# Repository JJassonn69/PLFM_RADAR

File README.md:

# AERIS-10: Open Source Pulse Linear Frequency Modulated Phased Array Radar

AERIS-10 is an open-source, low-cost 10.5 GHz phased array radar system featuring Pulse Linear Frequency Modulated (LFM) modulation. Available in two versions (3km and 20km range), it's designed for researchers, drone developers, and serious SDR enthusiasts who want to explore and experiment with phased array radar technology.

## 📡 Overview

The AERIS-10 project aims to democratize radar technology by providing a fully open-source, modular, and hackable radar system. Whether you're a university researcher, a drone startup, or an advanced maker, AERIS-10 offers a platform for experimenting with beamforming, pulse compression, Doppler processing, and target tracking.

## 🔬 Key Features

- **Open Source Hardware & Software** - Complete schematics, PCB layouts, firmware, and software available
- **Dual Version Availability**:
  - **AERIS-10N (Nexus)**: 3km range with 8x16 patch antenna array
  - **AERIS-10E (Extended)**: 20km range with 32x16 dielectric-filled slotted waveguide array
- **Full Electronic Beam Steering** - ±45° electronic steering in elevation and azimuth
- **Advanced Signal Processing** - On-board FPGA handles pulse compression, Doppler FFT, MTI, and CFAR
- **Python GUI** - User-friendly interface with map integration
- **GPS/IMU Integration** - Real-time position and attitude correction
- **Modular Design** - Separate power management, frequency synthesis, and RF boards

## 🏗️ System Architecture

### Hardware Components

The AERIS-10 main sub-systems are:

- **Power Management Board** - Supplies all necessary voltage levels to the electronics components with proper filtering and sequencing (sequencing ensured by the microcontroller)

- **Frequency Synthesizer Board** - Uses a high-performance Low Jitter Clock Generator (AD9523-1) that supplies phase-aligned clock references for:
  - RX and TX Frequency Synthesizers (ADF4382)
  - DAC
  - ADC
  - FPGA

- **Main Board** containing:
  - **DAC** - Generates the RADAR Chirps
  - **2x Microwave Mixers (LTC5552)** - For up-conversion and IF-down-conversion
  - **4x 4-Channel Phase Shifters (ADAR1000)** - For RX and TX chain beamforming
  - **16x Front End Chips (ADTR1107)** - Used for both Low Noise Amplifying (RX) and Power Amplifying (TX) stages
  - **XC7A50T FPGA** - Handles RADAR Signal Processing on the upstream FTG256 board:
    - PLFM Chirps generation via the DAC
    - Raw ADC data read
    - Hybrid Automatic Gain Control (AGC) — cross-layer FPGA/STM32/GUI loop
    - I/Q Baseband Down-Conversion
    - Decimation
    - Filtering
    - Forward FFT
    - Pulse Compression
    - Doppler, MTI and CFAR processing
    - USB Interface
  - **STM32F746xx Microcontroller** - Used for:
    - Power-up and power-down sequencing (see Power Management Excel File)
    - FPGA communication
    - Setup and Interface with:
      - Clock Generator (AD9523-1)
      - 2x Frequency Synthesizers (ADF4382)
      - 4x 4-Channel Phase Shifters (ADAR1000) for RADAR pulse sequencing
      - 2x ADS7830 8-channel I²C ADCs (Main Board, U88 @ 0x48 / U89 @ 0x4A) for 16x Idq measurement, one per PA channel, each sensed through a 5 mΩ shunt on the PA board and an INA241A3 current-sense amplifier (x50) on the Main Board
      - 2x DAC5578 8-channel I²C DACs (Main Board, U7 @ 0x48 / U69 @ 0x49) for 16x Vg control, one per PA channel; closed-loop calibrated at boot to the target Idq
      - GPS module (UM982) for GUI map centering and per-detection position tagging
      - GY-85 IMU for pitch/roll correction of target coordinates
      - BMP180 Barometer
      - Stepper Motor
      - 1x ADS7830 8-channel I²C ADC (Main Board, U10) reading 8 thermistors for thermal monitoring; a single GPIO (EN_DIS_COOLING) switches the cooling fans on when any channel exceeds the threshold
      - RF switches

- **16x Power Amplifier Boards** - Used only for AERIS-10E version, featuring 10Watt QPA2962 GaN amplifier for extended range

- **Antenna Arrays**:
  - **AERIS-10N (Nexus)** - 8x16 patch antenna array
  - **AERIS-10X (Extended)** - 32x16 dielectric-filled slotted waveguide antenna array

- **Miscellaneous Components**:
  - Slip-Ring
  - Stepper Motor and drivers
  - Cooling Fans
  - Enclosure

### Processing Pipeline

1. **Waveform Generation** - DAC creates LFM chirps
2. **Up/Down Conversion** - LTC5552 mixers handle frequency translation
3. **Beam Steering** - ADAR1000 phase shifters control 16 elements
4. **Signal Processing (FPGA)**:
   - Raw ADC data capture
   - I/Q baseband down-conversion
   - Decimation & filtering (CIC/FIR)
   - Pulse compression
   - Doppler FFT processing
   - MTI & CFAR detection
5. **System Management (STM32)**:
   - Power sequencing
   - Peripheral configuration
   - GPS/IMU integration
   - Stepper motor control
6. **Visualization (Python GUI)**:
   - Real-time target plotting
   - Map integration
   - Radar control interface

<!-- V6 GIF removed — V6 is deprecated. V65 Tk and V7 PyQt6 are the active GUIs. -->

## 📊 Technical Specifications

| Parameter | AERIS-10N (Nexus) | AERIS-10X (Extended) |
|-----------|-------------------|----------------------|
| **Frequency** | 10.5 GHz | 10.5 GHz |
| **Max Range** | 3 km | 20 km |
| **Antenna** | 8x16 Patch Array | 32x16 Slotted Waveguide |
| **Beam Steering** | Electronic (±45°) | Electronic (±45°) |
| **Mechanical Scan** | 360° (stepper motor) | 360° (stepper motor) |
| **Output Power** | ~1W×16 | 10W×16 (GaN amplifier) |
| **Processing** | FPGA + STM32 | FPGA + STM32 |

## 🚀 Getting Started

### 🧹 Repository File Placement Policy

To keep the repository root clean and make artifacts easy to find, place generated files in the following locations:

- **Published reports (tracked, GitHub Pages):** `docs/`
  - Example: `docs/AERIS_Simulation_Report_v2.pdf`
- **Simulation-generated outputs (local, gitignored):** `5_Simulations/generated/`
  - Plots, scenario outputs, temporary analysis directories
- **FPGA/Vivado generated artifacts (local, gitignored):** `9_Firmware/9_2_FPGA/reports/`
  - VCD/VVP dumps, temporary CSVs, local report snapshots
- **Reusable FPGA automation scripts (tracked):** `9_Firmware/9_2_FPGA/scripts/`
  - TCL flows, helper scripts used by build/bring-up

**Do not leave generated artifacts in the repository root.**

### Prerequisites

- Basic understanding of radar principles
- Experience with PCB assembly (for hardware build)
- Python 3.8+ for the GUI software
- FPGA development tools (Vivado) for signal processing modifications

### Hardware Assembly

1. **Order PCBs**: Production outputs are under `/4_Schematics and Boards Layout/4_7_Production Files`
2. **Source Components**: BOM/CPL files are co-located under `/4_Schematics and Boards Layout/4_7_Production Files`
3. **Assembly**: Use the schematics in `/4_Schematics and Boards Layout/4_6_Schematics` together with the production outputs above; a standalone assembly guide is not currently tracked
4. **Antenna**: Choose appropriate array files for your target variant
5. **Enclosure**: Mechanical drawings currently live in `/8_Utils/Mechanical_Drawings`

## 📜 License

This project is open-source but uses **different licenses for hardware and software** to ensure proper legal coverage.

### Hardware Documentation
The hardware design files—including:
- Schematics and PCB layouts (in `/4_Schematics and Boards Layout`)
- Bill of Materials (BOM) files
- Gerber files and manufacturing outputs
- Mechanical drawings and enclosure designs

are licensed under the **CERN Open Hardware Licence Version 2 – Permissive (CERN-OHL-P)** .

This is a hardware-specific license that:
- ✅ Clearly defines "Hardware," "Documentation," and "Products"
- ✅ Includes explicit patent protection for contributors and users
- ✅ Provides stronger liability limitations (important for high-power RF)
- ✅ Aligns with professional open-hardware standards (CERN, OSHWA)

You may use, modify, and sell products based on these designs, provided you:
- Maintain the original copyright notices
- Distribute any modified designs under the same license
- Make your modifications available in Source format

### Software and Firmware
The software components—including:
- FPGA code (VHDL/Verilog in `/9_Firmware`)
- Microcontroller firmware (STM32)
- Python GUI and utilities

remain under the **MIT License** for maximum flexibility.

### Full License Texts
- The complete CERN-OHL-P license text is in the `LICENSE` file
- MIT license terms apply to software where not otherwise specified

### Why This Change?
Originally, the entire project used the MIT license. The community (special thanks to gmaynez!) pointed out that MIT lacks legal protections needed for physical hardware. The switch to CERN-OHL-P ensures the project is properly protected while maintaining the same permissive spirit.

## 📚 Documentation

Comprehensive documentation is available in the `/docs` folder and served via GitHub Pages at [https://NawfalMotii79.github.io/PLFM_RADAR/docs/](https://NawfalMotii79.github.io/PLFM_RADAR/docs/):

- [System Architecture](/docs/architecture.html)
- [Implementation Log](/docs/implementation-log.html)
- [Hardware Bring-Up Guide](/docs/bring-up.html)
- [Test Reports](/docs/reports.html)
- [Release Notes](/docs/release-notes.html)

## 🤝 Contributing

We welcome contributions! Please see our [Contributing Guidelines](/CONTRIBUTING.md) for details on repo layout, branch workflow, and basic PR checks.

Areas where help is especially appreciated:
- **RF Engineers**: Review designs, optimize antenna performance
- **FPGA Developers**: Optimize signal processing pipeline
- **Software Developers**: Enhance Python GUI and SDK
- **Beta Testers**: University researchers, drone startups, advanced makers

## 📞 Contact & Collaboration

I welcome serious inquiries from researchers, engineers, and potential collaborators. However, due to the high volume of interest in this project, please understand that I cannot guarantee a response to every message.

- **Technical questions or bug reports**: Please [open a GitHub issue](https://github.com/NawfalMotii79/PLFM_RADAR/issues) so the whole community can benefit from the discussion.
- **Collaboration, licensing, or business inquiries**: 📧 nawfal.motii.33 [at] gmail [dot] com

## 💰 Sponsors

---

**Star ⭐ this repository if you're interested in open-source radar technology!**

*Note: This is an active development project. Some features are still in progress. Check the issues page for known limitations and upcoming features.*

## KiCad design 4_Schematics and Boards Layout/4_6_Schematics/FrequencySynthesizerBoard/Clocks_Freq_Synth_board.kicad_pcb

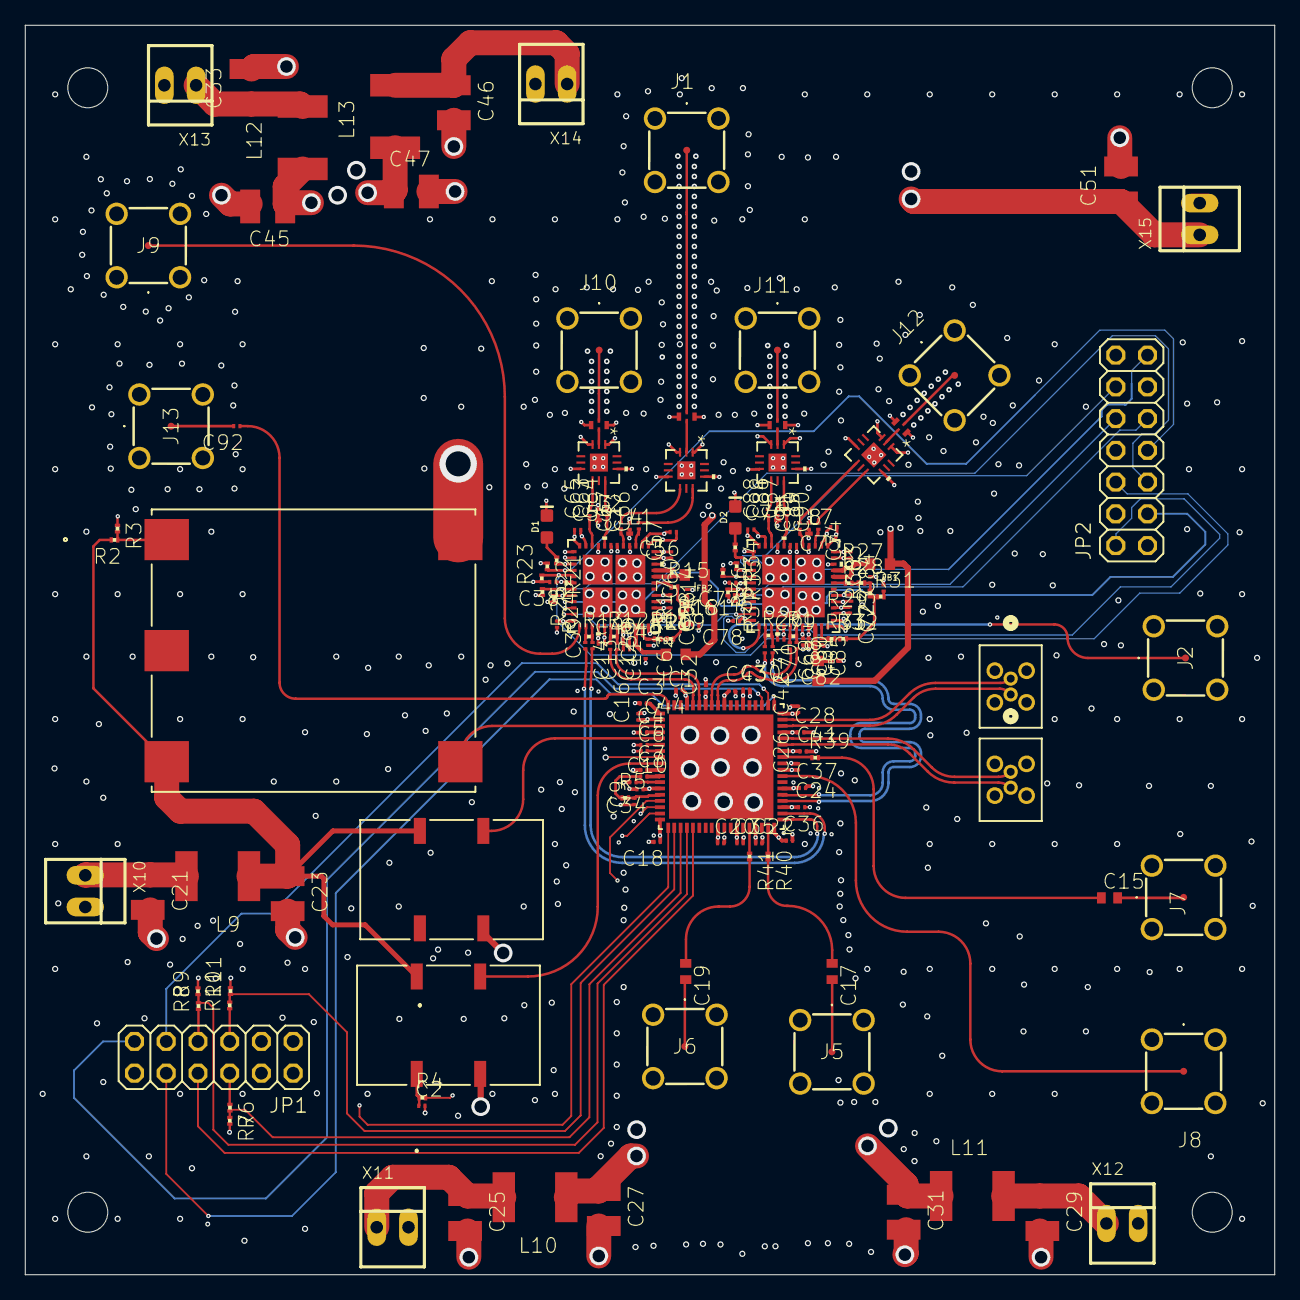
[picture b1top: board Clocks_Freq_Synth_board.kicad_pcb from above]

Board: 6 copper layers, 100.0 x 100.0 mm, 188 parts (0 on the bottom side), 134 nets.

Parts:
C1, C62, C63, C85, C86, C89: 10pF; C0201_334
C2, C6: 0.33µF; C0201_334
C3: 0.47µf; C0201_334
C4, C5, C7: C0201_334
C8: 1000pF; C0201_334
C9, C10: 0.47µF; C0201_334
C11, C12, C13, C14, C59, C68, C69, C70, C71, C82: 1µF; C0201_334
C15, C17, C19: 10nF; C0402_334
C16, C18, C20, C22, C24, C26, C28, C30, C32, C34, C35, C36, C37, C41, C42, C43, C44, C64, C65, C66, C67, C87, C88, C90, C91: 0.1µF; C0201_334
C21, C25, C29, C33, C46, C51: 22µF; C1210_334
C23, C27, C31, C45, C47: 10µF; C1210_334
C38, C39, C40, C48, C49, C50, C55, C56, C57, C58, C72, C73, C74, C75, C76, C77, C78, C79, C80, C81: 4.7µF; C0201_334
C60, C83: 31pF; C0201_334
C61, C84: 10nF; C0201_334
C92: 0.1µf; C0201_334
D1, D2: Green; LED-0603
FB1, FB2, FB3, FB4: FBMH1608HL601-T; BEADC1608X90N
IC1: AD9523BCPZ; QFN50P1000X1000X100-73N
J1, J2, J5, J6, J7, J8, J9, J10, J11, J12, J13: 142-0731-211; 1420731211
J3, J4: CJT-T-P-HH-ST-TH1; CONN_CJT-T-P-XX-ST-TH1_SAI
JP1: 2X06_325
JP2: 2X07_325
L1, L2, L3, L4, L5, L6, L7, L8: 1.3nH; L0201_334
L9, L10, L11, L12, L13: L5650M_334
R1, R12, R13, R26: 100R; R0201_334
R2, R3, R4, R7, R9, R11: 1k; R0201_334
R5, R14, R15, R19, R20, R27, R28, R32, R33: 0R; R0201_334
R6, R8, R10: 0.65k; R0201_334
R16, R29: 931R; R0201_334
R17, R30: 30R; R0201_334
R18, R31: 330R; R0201_334
R21, R34: 500R; R0201_334
R22, R23, R24, R25, R35, R36, R37, R38: 200k; R0201_334
R39, R40, R41: 22R; R0201_334
U1, U6: ADF4382ABCCZ; CC-48-10_ADI
U2, U3, U7, U9: MTX2-143+; DQ1225_MNC
U4, U5, U8, U10: ATS1005-3DB-FD-T05; SMT_DB-FD-T05_SUS
UNK_HOLE_0: dummyfp0
UNK_HOLE_1: dummyfp1
UNK_HOLE_2: dummyfp2
UNK_HOLE_3: dummyfp3
X4: ECOC-2522-100.000-3HC; SMD5_ECOC-2522_25P4X22_ECS
X5, X6: CVHD-950-50.000; SMD4_CVHD-950_CRX
X10, X11, X12, X13, X14, X15: 22-23-2021; 22-23-2021_165

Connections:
10MHZ_OUT: IC1.3, X4.4
100MHZ_OUT: IC1.5, X5.3
+1V8_CLOCK: C31.1, C35.1, C36.1, C37.1, C41.1, C42.1, C43.1, C44.1, IC1.30, IC1.36, IC1.42, IC1.48, IC1.54, IC1.63, IC1.69, L11.1
+3V3_CLOCK: C16.1, C18.1, C20.1, C22.1, C24.1, C26.1, C27.1, C28.1, C30.1, C32.1, C34.1, IC1.2, IC1.13, IC1.18, IC1.27, IC1.33, IC1.39, IC1.45, IC1.51, IC1.60, IC1.66, L10.1
+3V3_LO_1: C38.1, C39.1, C40.1, C45.1, C48.1, C49.1, C50.1, C72.1, C77.1, C78.1, C79.1, C80.1, C81.1, L12.1, R24.2, R25.2, R37.2, R38.2, U1.3, U1.30, U1.36, U1.40, U1.44, U1.45, U6.3, U6.30, U6.36, U6.40, U6.44, U6.45
+3V3_LO_2: C1.1, C47.1, C55.1, C56.1, C57.1, C58.1, C63.1, C73.1, C74.1, C75.1, C76.1, C86.1, C89.1, L1.1, L2.1, L3.2, L4.2, L5.1, L6.2, L7.1, L8.2, L13.1, U1.5, U1.11, U1.13, U1.24, U6.5, U6.11, U6.13, U6.24
+3V3_XO: C23.1, L9.1, R2.2, X4.3, X5.4, X6.4
+5V0_LO: C51.1, FB1.1, FB2.1, FB3.2, FB4.2, X15.1
AD9523_CS: JP1.5, R10.1
AD9523_EEPROM_SEL: IC1.57, JP1.11
AD9523_OUT0_N: C11.2, IC1.67
AD9523_OUT0_P: C12.2, IC1.68
AD9523_OUT1_N: C68.2, IC1.64
AD9523_OUT1_P: C69.2, IC1.65
AD9523_OUT4_N: IC1.52, J3.2
AD9523_OUT4_P: IC1.53, J3.1
AD9523_OUT5_N: IC1.49, J4.2
AD9523_OUT5_P: IC1.50, J4.1
AD9523_OUT6+: C15.2, J7.1
AD9523_OUT7+: IC1.44, J8.1
AD9523_OUT8_N: C70.2, IC1.40
AD9523_OUT8_P: C71.2, IC1.41
AD9523_OUT9_N: C13.2, IC1.37
AD9523_OUT9_P: C14.2, IC1.38
AD9523_OUT10+: IC1.35, R40.1
AD9523_OUT11+: IC1.32, R41.1
AD9523_PD: IC1.15, JP1.1
AD9523_REF_SEL: IC1.16, JP1.2
AD9523_RESET: IC1.19, JP1.4
AD9523_SCLK: JP1.6, R6.1
AD9523_SDIO: JP1.7, R8.1
AD9523_SDO: IC1.23, JP1.8
AD9523_STATUS0: IC1.56, JP1.9
AD9523_STATUS1: IC1.55, JP1.10
AD9523_SYNC: IC1.17, JP1.3
ADF4382_RX_CE: JP2.10, R38.1, U6.31
ADF4382_RX_CS: JP2.9, R37.1, U6.32
ADF4382_RX_DELADJ: JP2.12, R35.2, U6.28
ADF4382_RX_DELSTR: JP2.11, R36.2, U6.29
ADF4382_RX_LKDET: JP2.13, R34.2, U6.27
ADF4382_RX_SYNC_N: C70.1, R26.2, U6.39
ADF4382_RX_SYNC_P: C71.1, R26.1, U6.38
ADF4382_SCLK: JP2.2, U1.34, U6.34
ADF4382_SDIO: JP2.3, U1.33, U6.33
ADF4382_SDO: JP2.1, U1.35, U6.35
ADF4382_TX_CE: JP2.5, R25.1, U1.31
ADF4382_TX_CS: JP2.4, R24.1, U1.32
ADF4382_TX_DELADJ: JP2.7, R22.2, U1.28
ADF4382_TX_DELSTR: JP2.6, R23.2, U1.29
ADF4382_TX_LKDET: JP2.8, R21.2, U1.27
ADF4382_TX_SYNC_N: C13.1, R13.2, U1.39
ADF4382_TX_SYNC_P: C14.1, R13.1, U1.38
GND: C1.2, C2.2, C3.1, C4.1, C5.1, C6.1, C7.1, C9.1, C10.1, C16.2, C18.2, C20.2, C21.2, C22.2, C23.2, C24.2, C25.2, C26.2, C27.2, C28.2, C29.2, C30.2, C31.2, C32.2, C33.2, C34.2, C35.2, C36.2, C37.2, C38.2, C39.2, C40.2, C41.2, C42.2, C43.2, C44.2, C45.2, C46.2, C47.2, C48.2, C49.2, C50.2, C51.2, C55.2, C56.2, C57.2, C58.2, C59.1, C60.2, C61.2, C62.2, C63.2, C72.2, C73.2, C74.2, C75.2, C76.2, C77.2, C78.2, C79.2, C80.2, C81.2, C82.1, C83.2, C84.2, C85.2, C86.2, C89.2, D1.C, D2.C, IC1.73, J1.2, J1.3, J1.4, J1.5, J2.2, J2.3, J2.4, J2.5, J5.2, J5.3, J5.4, J5.5, J6.2, J6.3, J6.4, J6.5, J7.2, J7.3, J7.4, J7.5, J8.2, J8.3, J8.4, J8.5, J9.2, J9.3, J9.4, J9.5, J10.2, J10.3, J10.4, J10.5, J11.2, J11.3, J11.4, J11.5, J12.2, J12.3, J12.4, J12.5, J13.2, J13.3, J13.4, J13.5, JP1.12, JP2.14, R3.1, R7.2, R9.2, R11.2, R22.1, R23.1, R35.1, R36.1, U1.1, U1.2, U1.4, U1.10, U1.12, U1.14, U1.16, U1.18, U1.19, U1.21, U1.23, U1.25, U1.26, U1.41, U1.48, U1.49, U1.50, U1.51, U1.52, U2.1, U2.3, U2.6, U2.10, U2.13, U3.1, U3.3, U3.6, U3.10, U3.13, U4.3, U4.4, U5.3, U5.4, U6.1, U6.2, U6.4, U6.10, U6.12, U6.14, U6.16, U6.18, U6.19, U6.21, U6.23, U6.25, U6.26, U6.41, U6.48, U6.49, U6.50, U6.51, U6.52, U7.1, U7.3, U7.6, U7.10, U7.13, U8.3, U8.4, U9.1, U9.3, U9.6, U9.10, U9.13, U10.3, U10.4, X4.5, X5.2, X6.2, X10.2, X11.2, X12.2, X13.2, X14.2, X15.2
unnamed: R2.1, R3.2, X4.1
unnamed: C2.1, R4.1, X6.1
unnamed: C3.2, IC1.1
unnamed: C6.2, IC1.7
unnamed: C4.2, IC1.4
unnamed: C5.2, IC1.6
unnamed: C7.2, IC1.10
unnamed: C8.2, IC1.11
unnamed: C8.1, R5.1
unnamed: C9.2, IC1.14, R5.2
unnamed: C10.2, IC1.12
unnamed: IC1.21, R6.2, R7.1
unnamed: IC1.22, R8.2, R9.1
unnamed: IC1.20, R10.2, R11.1
unnamed: C11.1, R12.2, U1.43
unnamed: C12.1, R12.1, U1.42
unnamed: C61.1, R18.2
unnamed: R14.1, U1.9
unnamed: FB2.2, R14.2, U1.8
unnamed: C59.2, FB3.1, U1.46
unnamed: R19.1, R20.2
unnamed: R15.1, U1.7
unnamed: R15.2, R16.2
unnamed: C60.1, R16.1, R17.2
unnamed: R17.1, R18.1, R19.2
unnamed: C62.1, R20.1, U1.47
unnamed: U2.2, U4.1
unnamed: C65.2, U2.7
unnamed: J10.1, U4.2
unnamed: C64.2, U2.9
unnamed: C67.2, U3.7
unnamed: C66.2, U3.9
unnamed: U3.2, U5.1
unnamed: J1.1, U5.2
unnamed: D1.A, R21.1
unnamed: J9.1, U1.37
unnamed: C68.1, R1.2, U6.43
unnamed: C69.1, R1.1, U6.42
unnamed: R27.1, U6.9
unnamed: FB1.2, R27.2, U6.8
unnamed: C82.2, FB4.1, U6.46
unnamed: C84.1, R31.2
unnamed: R32.1, R33.2
unnamed: R28.1, U6.7
unnamed: R28.2, R29.2
unnamed: C83.1, R29.1, R30.2
unnamed: R30.1, R31.1, R32.2
unnamed: C85.1, R33.1, U6.47
unnamed: D2.A, R34.1
unnamed: J2.1, U6.37
unnamed: C88.2, U7.7
unnamed: C87.2, U7.9
unnamed: U7.2, U8.1
unnamed: J11.1, U8.2
unnamed: C91.2, U9.7
unnamed: C90.2, U9.9
unnamed: U9.2, U10.1
unnamed: J12.1, U10.2
unnamed: C92.1, IC1.72
unnamed: C92.2, J13.1
unnamed: IC1.47, R39.1
unnamed: C15.1, R39.2
unnamed: C17.2, J5.1
unnamed: C17.1, R40.2
unnamed: C19.2, J6.1
unnamed: C19.1, R41.2
unnamed: C21.1, L9.2, X10.1
unnamed: C25.1, L10.2, X11.1
unnamed: C29.1, L11.2, X12.1
unnamed: C33.1, L12.2, X13.1
unnamed: C46.1, L13.2, X14.1
OSC_CTRL: IC1.8, R4.2
RX_RFOUT_1_N: C87.1, L5.2, U6.20
RX_RFOUT_1_P: C88.1, L6.1, U6.22
RX_RFOUT_2_N: C90.1, L7.2, U6.15
RX_RFOUT_2_P: C91.1, L8.1, U6.17
TX_RFOUT_1_N: C64.1, L2.2, U1.20
TX_RFOUT_1_P: C65.1, L3.1, U1.22
TX_RFOUT_2_N: C66.1, L1.2, U1.15
TX_RFOUT_2_P: C67.1, L4.1, U1.17
VCXO_OUT: IC1.9, X6.3

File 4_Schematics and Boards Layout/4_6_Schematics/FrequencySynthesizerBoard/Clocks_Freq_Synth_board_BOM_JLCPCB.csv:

Comment,Designator,Footprint,LCSC Part #
10pF,"C1,C62,C63,C85,C86,C89",C0201_334,C106245
0.33µF,"C2,C6",C0201_334,C331029
0.47µf,C3,C0201_334,C331025
DNP,"C4,C5,C7",C0201_334,
1000pF,C8,C0201_334,C106246
0.47µF,"C9,C10",C0201_334,C331025
1µF,"C11,C12,C13,C14,C59,C68,C69,C70,C71,C82",C0201_334,C106253
10nF,"C15,C17,C19",C0402_334,C15195
0.1µF,"C16,C18,C20,C22,C24,C26,C28,C30,C32,C34,C35,C36,C37,C41,C42,C43,C44,C64,C65,C66,C67,C87,C88,C90,C91",C0201_334,C106250
22µF,"C21,C25,C29,C33,C46,C51",C1210_334,C108816
10µF,"C23,C27,C31,C45,C47",C1210_334,C108812
4.7µF,"C38,C39,C40,C48,C49,C50,C55,C56,C57,C58,C72,C73,C74,C75,C76,C77,C78,C79,C80,C81",C0201_334,C106258
31pF,"C60,C83",C0201_334,
10nF,"C61,C84",C0201_334,C106247
0.1µf,C92,C0201_334,C106250
Green,"D1,D2",LED-0603,C72043
FBMH1608HL601-T,"FB1,FB2,FB3,FB4",BEADC1608X90N,C96445
AD9523BCPZ,IC1,QFN50P1000X1000X100-73N,
142-0731-211,"J1,J2,J5,J6,J7,J8,J9,J10,J11,J12,J13",1420731211,
CJT-T-P-HH-ST-TH1,"J3,J4",CONN_CJT-T-P-XX-ST-TH1_SAI,
DNP,JP1,2X06_325,
DNP,JP2,2X07_325,
1.3nH,"L1,L2,L3,L4,L5,L6,L7,L8",L0201_334,
DNP,"L9,L10,L11,L12,L13",L5650M_334,
100R,"R1,R12,R13,R26",R0201_334,C106230
1k,"R2,R3,R4,R7,R9,R11",R0201_334,C106232
0R,"R5,R14,R15,R19,R20,R27,R28,R32,R33",R0201_334,C106222
0.65k,"R6,R8,R10",R0201_334,
931R,"R16,R29",R0201_334,
30R,"R17,R30",R0201_334,C106228
330R,"R18,R31",R0201_334,C106231
500R,"R21,R34",R0201_334,
200k,"R22,R23,R24,R25,R35,R36,R37,R38",R0201_334,C106240
22R,"R39,R40,R41",R0201_334,C106227
ADF4382ABCCZ,"U1,U6",CC-48-10_ADI,
MTX2-143+,"U2,U3,U7,U9",DQ1225_MNC,
ATS1005-3DB-FD-T05,"U4,U5,U8,U10",SMT_DB-FD-T05_SUS,
ECOC-2522-100.000-3HC,X4,SMD5_ECOC-2522_25P4X22_ECS,
CVHD-950-50.000,"X5,X6",SMD4_CVHD-950_CRX,
22-23-2021,"X10,X11,X12,X13,X14,X15",22-23-2021_165,

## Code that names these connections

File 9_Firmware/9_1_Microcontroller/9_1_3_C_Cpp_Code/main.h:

/* USER CODE BEGIN Header */
/**
  ******************************************************************************
  * @file           : main.h
  * @brief          : Header for main.c file.
  *                   This file contains the common defines of the application.
  ******************************************************************************
  * @attention
  *
  * Copyright (c) 2025 STMicroelectronics.
  * All rights reserved.
  *
  * This software is licensed under terms that can be found in the LICENSE file
  * in the root directory of this software component.
  * If no LICENSE file comes with this software, it is provided AS-IS.
  *
  ******************************************************************************
  */
/* USER CODE END Header */

/* Define to prevent recursive inclusion -------------------------------------*/
#ifndef __MAIN_H
#define __MAIN_H

#ifdef __cplusplus
extern "C" {
#endif

/* Includes ------------------------------------------------------------------*/
#include "stm32f7xx_hal.h"

/* Private includes ----------------------------------------------------------*/
/* USER CODE BEGIN Includes */

/* USER CODE END Includes */

/* Exported types ------------------------------------------------------------*/
/* USER CODE BEGIN ET */
extern uint8_t GUI_start_flag_received;
extern uint8_t USB_Buffer[64];

/* USER CODE END ET */

/* Exported constants --------------------------------------------------------*/
/* USER CODE BEGIN EC */

/* USER CODE END EC */

/* Exported macro ------------------------------------------------------------*/
/* USER CODE BEGIN EM */

/* USER CODE END EM */

/* Exported functions prototypes ---------------------------------------------*/
void Error_Handler(void);

/* USER CODE BEGIN EFP */

/* USER CODE END EFP */

/* Private defines -----------------------------------------------------------*/
#define AD9523_PD_Pin GPIO_PIN_3
#define AD9523_PD_GPIO_Port GPIOF
#define AD9523_REF_SEL_Pin GPIO_PIN_4
#define AD9523_REF_SEL_GPIO_Port GPIOF
#define AD9523_SYNC_Pin GPIO_PIN_5
#define AD9523_SYNC_GPIO_Port GPIOF
#define AD9523_RESET_Pin GPIO_PIN_6
#define AD9523_RESET_GPIO_Port GPIOF
#define AD9523_CS_Pin GPIO_PIN_7
#define AD9523_CS_GPIO_Port GPIOF
#define AD9523_STATUS0_Pin GPIO_PIN_8
#define AD9523_STATUS0_GPIO_Port GPIOF
#define AD9523_STATUS1_Pin GPIO_PIN_9
#define AD9523_STATUS1_GPIO_Port GPIOF
#define AD9523_EEPROM_SEL_Pin GPIO_PIN_10
#define AD9523_EEPROM_SEL_GPIO_Port GPIOF
#define ADAR_1_CS_3V3_Pin GPIO_PIN_0
#define ADAR_1_CS_3V3_GPIO_Port GPIOA
#define ADAR_2_CS_3V3_Pin GPIO_PIN_1
#define ADAR_2_CS_3V3_GPIO_Port GPIOA
#define ADAR_3_CS_3V3_Pin GPIO_PIN_2
#define ADAR_3_CS_3V3_GPIO_Port GPIOA
#define ADAR_4_CS_3V3_Pin GPIO_PIN_3
#define ADAR_4_CS_3V3_GPIO_Port GPIOA
#define LED_1_Pin GPIO_PIN_12
#define LED_1_GPIO_Port GPIOF
#define LED_2_Pin GPIO_PIN_13
#define LED_2_GPIO_Port GPIOF
#define LED_3_Pin GPIO_PIN_14
#define LED_3_GPIO_Port GPIOF
#define LED_4_Pin GPIO_PIN_15
#define LED_4_GPIO_Port GPIOF
#define EN_P_5V0_PA1_Pin GPIO_PIN_0
#define EN_P_5V0_PA1_GPIO_Port GPIOG
#define EN_P_5V0_PA2_Pin GPIO_PIN_1
#define EN_P_5V0_PA2_GPIO_Port GPIOG
#define EN_P_1V0_FPGA_Pin GPIO_PIN_7
#define EN_P_1V0_FPGA_GPIO_Port GPIOE
#define EN_P_1V8_FPGA_Pin GPIO_PIN_8
#define EN_P_1V8_FPGA_GPIO_Port GPIOE
#define EN_P_3V3_FPGA_Pin GPIO_PIN_9
#define EN_P_3V3_FPGA_GPIO_Port GPIOE
#define EN_P_5V0_ADAR_Pin GPIO_PIN_10
#define EN_P_5V0_ADAR_GPIO_Port GPIOE
#define EN_P_3V3_ADAR12_Pin GPIO_PIN_11
#define EN_P_3V3_ADAR12_GPIO_Port GPIOE
#define EN_P_3V3_ADAR34_Pin GPIO_PIN_12
#define EN_P_3V3_ADAR34_GPIO_Port GPIOE
#define EN_P_3V3_ADTR_Pin GPIO_PIN_13
#define EN_P_3V3_ADTR_GPIO_Port GPIOE
#define EN_P_3V3_SW_Pin GPIO_PIN_14
#define EN_P_3V3_SW_GPIO_Port GPIOE
#define EN_P_3V3_VDD_SW_Pin GPIO_PIN_15
#define EN_P_3V3_VDD_SW_GPIO_Port GPIOE
#define EN_P_5V0_PA3_Pin GPIO_PIN_2
#define EN_P_5V0_PA3_GPIO_Port GPIOG
#define EN_P_5V5_PA_Pin GPIO_PIN_3
#define EN_P_5V5_PA_GPIO_Port GPIOG
#define EN_P_1V8_CLOCK_Pin GPIO_PIN_4
#define EN_P_1V8_CLOCK_GPIO_Port GPIOG
#define EN_P_3V3_CLOCK_Pin GPIO_PIN_5
#define EN_P_3V3_CLOCK_GPIO_Port GPIOG
#define ADF4382_RX_LKDET_Pin GPIO_PIN_6
#define ADF4382_RX_LKDET_GPIO_Port GPIOG
#define ADF4382_RX_DELADJ_Pin GPIO_PIN_7
#define ADF4382_RX_DELADJ_GPIO_Port GPIOG
#define ADF4382_RX_DELSTR_Pin GPIO_PIN_8
#define ADF4382_RX_DELSTR_GPIO_Port GPIOG
#define MAG_DRDY_Pin GPIO_PIN_6
#define MAG_DRDY_GPIO_Port GPIOC
#define ACC_INT_Pin GPIO_PIN_7
#define ACC_INT_GPIO_Port GPIOC
#define GYR_INT_Pin GPIO_PIN_8
#define GYR_INT_GPIO_Port GPIOC
#define STEPPER_CW_P_Pin GPIO_PIN_4
#define STEPPER_CW_P_GPIO_Port GPIOD
#define STEPPER_CLK_P_Pin GPIO_PIN_5
#define STEPPER_CLK_P_GPIO_Port GPIOD
#define EN_DIS_RFPA_VDD_Pin GPIO_PIN_6
#define EN_DIS_RFPA_VDD_GPIO_Port GPIOD
#define EN_DIS_COOLING_Pin GPIO_PIN_7
#define EN_DIS_COOLING_GPIO_Port GPIOD

/* FPGA digital I/O (directly connected GPIOs)
 *   DIG_5 (PD13): signal-saturation flag — input, polled by AGC outer loop
 *                 (gated by !MCU_AGC_FORCE_DISABLED).
 *   DIG_6 (PD14): chirp_scheduler frame_pulse, ~100 ns FPGA-stretched —
 *                 EXTI rising + pulldown; ISR increments g_frame_pulse_count
 *                 (PR-AB.b drift-free dwell sync).
 *   DIG_7 (PD15): control-fault OR (range_decim_watchdog | CIC→FIR overrun) —
 *                 polled by checkSystemHealth stuck-high sampler. */
#define FPGA_DIG5_SAT_Pin       GPIO_PIN_13
#define FPGA_DIG5_SAT_GPIO_Port GPIOD
#define FPGA_DIG6_Pin           GPIO_PIN_14
#define FPGA_DIG6_GPIO_Port     GPIOD
#define FPGA_DIG7_Pin           GPIO_PIN_15
#define FPGA_DIG7_GPIO_Port     GPIOD

/* PR-AB.b: alias names that match the post-Phase-3 role of DIG_6. */
#define FPGA_FRAME_PULSE_Pin       FPGA_DIG6_Pin
#define FPGA_FRAME_PULSE_GPIO_Port FPGA_DIG6_GPIO_Port
#define FPGA_FRAME_PULSE_EXTI_IRQn EXTI15_10_IRQn

/* PR-AB.b expanded commit 5: DIG_0 (PD8) carries the MCU per-beam-pattern
 * ready toggle into the FPGA's chirp_scheduler beam-ready handshake.
 * runRadarPulseSequence toggles this pin once per setCustomBeamPattern16(RX)
 * call after the SPI burst completes, so the FPGA only starts the next 48-
 * chirp frame once the new beam pattern is in place. The FPGA-side stall is
 * gated by opcode 0x1A (host_handshake_enable, cold-reset = 0) so flashing
 * the bitstream before the GUI enables the feature leaves the radar in its
 * legacy open-loop cadence. */
#define FPGA_BEAM_READY_Pin       GPIO_PIN_8
#define FPGA_BEAM_READY_GPIO_Port GPIOD

#define ADF4382_RX_CE_Pin GPIO_PIN_9
#define ADF4382_RX_CE_GPIO_Port GPIOG
#define ADF4382_RX_CS_Pin GPIO_PIN_10
#define ADF4382_RX_CS_GPIO_Port GPIOG
#define ADF4382_TX_LKDET_Pin GPIO_PIN_11
#define ADF4382_TX_LKDET_GPIO_Port GPIOG
#define ADF4382_TX_DELSTR_Pin GPIO_PIN_12
#define ADF4382_TX_DELSTR_GPIO_Port GPIOG
#define ADF4382_TX_DELADJ_Pin GPIO_PIN_13
#define ADF4382_TX_DELADJ_GPIO_Port GPIOG
#define ADF4382_TX_CS_Pin GPIO_PIN_14
#define ADF4382_TX_CS_GPIO_Port GPIOG
#define ADF4382_TX_CE_Pin GPIO_PIN_15
#define ADF4382_TX_CE_GPIO_Port GPIOG
#define DAC_1_VG_CLR_Pin GPIO_PIN_4
#define DAC_1_VG_CLR_GPIO_Port GPIOB
#define DAC_1_VG_LDAC_Pin GPIO_PIN_5
#define DAC_1_VG_LDAC_GPIO_Port GPIOB
#define DAC_2_VG_CLR_Pin GPIO_PIN_8
#define DAC_2_VG_CLR_GPIO_Port GPIOB
#define DAC_2_VG_LDAC_Pin GPIO_PIN_9
#define DAC_2_VG_LDAC_GPIO_Port GPIOB

/* USER CODE BEGIN Private defines */

/* USER CODE END Private defines */

#ifdef __cplusplus
}
#endif

#endif /* __MAIN_H */

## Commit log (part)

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2026-03-20 Complete Diagram
2026-03-22 Add board-day smoke test guide with step-by-step instructions
    Covers:
    - Bitstream inventory (heartbeat v0.1.7, FT601 dev v0.1.8, timing-fix v0.1.9)
    - Hardware setup: TE0713 + TE0701 + UMFT601X-B jumper config
    - 3-stage smoke test: heartbeat → FT601 USB → host commands
    - Host-side smoke_test.py and radar_dashboard.py usage
    - Signal diagnostics table, troubleshooting, known limitations
2026-03-22 Revert "Fix Ctrl+C crash in radar_dashboard.py (GIL + tkinter threading race)"
    This reverts commit 7f0e7b4cac3175e6660dc97f5b219f5a3faf1495.
2026-03-22 Clarify detection scatter coordinate mapping after fftshift
    Add explicit comments explaining how shifted Doppler array indices
    map to velocity coordinates. The coordinate conversion was correct,
    but now it's documented:
    - Shifted index 0 = original bin 16 = -max_vel (most negative)
    - Shifted index 16 = original bin 0 = 0 m/s (DC)
    - Shifted index 31 = original bin 15 = +max_vel (most positive)
2026-03-22 Add --moving-target mode: approaching target with closing range
    Reverted packet alignment fix since diagonal waterfall is correct
    for moving targets (range changes over time = diagonal stripes).
    New --moving-target flag simulates target approaching radar:
    - Target starts at range bin 55 (far, ~280m)
    - Moves toward radar at 0.3 bins/frame (negative velocity)
    - High positive Doppler (Doppler bin 25 = approaching fast)
2026-03-22 Add JLCPCB project rules and refine DRC: 1508 -> 661 violations (9 real errors)
    - Create .kicad_pro with JLCPCB 6-layer design rules (0.1mm clearance,
    0.3mm min via, 0.075mm annular ring, 0.15mm drill/hole)
    - Update .kicad_dru: relax via-to-via clearance from 0.254mm to 0.20mm
    (JLCPCB minimum for 0.15mm drill), eliminating 16 false positives
    - Rewrite DRC fix guide with verified violation counts and streamlined
    path to fab-ready (~30 min manual work remaining)
2026-03-23 Add freq synth board: schematic, gerbers, drills, BOM, DRC-fixed PCB
    Includes:
    - Restored schematic (.kicad_sch) from Eagle import history
    - Sub-schematic sheet (_1.kicad_sch)
    - Eagle import symbol library (.kicad_sym)
    - JLCPCB 6-layer gerber set (F/B/In1-4 Cu, masks, paste, silkscreen)
    - PTH + NPTH drill files with drill map PDF
2026-03-23 Repo cleanup: remove duplicate files, root fix scripts, update README paths
    Deleted (duplicates — identical MD5 copies exist elsewhere):
    - 8_Utils/Antenna_Array.jpg (dup of docs/assets/img/Antenna_Array.jpg)
    - 8_Utils/RADAR_V6.jpg (dup of docs/assets/img/RADAR_V6.jpg)
    - 8_Utils/RADAR_V6_V2.png (dup of 2_Functional Diagram/RADAR_V6_V2.png)
    - 8_Utils/Python/test_radar_data.csv (dup of 9_Firmware/9_3_GUI/test_radar_data.csv)
    - 7_Components Datasheets/AD9484/UG-290.pdf (dup of 6_Application Notes/UG-290.pdf)
2026-03-24 Fix velocity flip: per-dimension clustering + SNR-weighted centroid
    Root cause: euclidean eps=50 merged all detections at same range
    regardless of velocity, causing 48 detections (-24 to +24 m/s) to
    merge into one cluster with meaningless average velocity.
    Fix:
    - Per-dimension box thresholds (range_eps=20m, vel_eps=5m/s)
    - Sort by SNR descending so strongest peaks seed clusters
2026-03-24 Fix UART pin mapping: P16 -> P19 for uart_rxd (MIO14/B14_L24_P)
    Verified via 4x5_series_pinout_tracelength.xlsx that:
    - JB1-91 (MIO14) -> JM1-92 -> FPGA P19 (B14_L24_P), NOT P16
    - JB1-86 (MIO15) -> JM1-85 -> FPGA U18 (B14_L18_N) (was correct)
    Both nets are direct B2B-to-FPGA, NOT routed through TE0713 CPLD U3.
2026-03-24 Fix VIO build: create IP directory before create_ip
2026-03-25 Add GO/SO CFAR mode dropdown, parameter validation, and fix tkinter test deps
    V2 dashboard enhancements:
    - Replace CFAR Mode numeric entry with CA/GO/SO dropdown (ttk.Combobox)
    - Add _send_validated_param() with RTL-accurate range clamping for all params
    - Add CFAR mode indicator in status bar
    Shared constants extracted to radar_protocol.py (tkinter-free):
    - CFAR_MODE_NAMES, CFAR_MODE_VALUES, PARAM_VALIDATION, AERIS10_CONFIG
2026-03-27 Add TCP stream server for remote FPGA visualization over SSH tunnel
    New SocketConnection class in radar_protocol.py provides the same
    interface as FT601Connection but communicates over TCP with a
    length-prefixed protocol. ft601_stream_server.py runs on the remote
    server (with FT601 hardware) and bridges USB reads/writes to TCP.
    Usage: start server on remote, SSH tunnel port 9000, then:
    python3 GUI_radar_dashboard_v2.py --remote localhost:9000
2026-03-28 FPGA v9d: fix Pop FSM pending flag races + USB drain timing
    - Add !usb_X_pending guards to all 3 Pop FSMs (prevents pop-while-pending)
    - Add disabled-stream discard logic in USB FSM IDLE state (prevents deadlock)
    - Add per-type RTL debug counters (consumed/discarded/pending_sets)
    - Fix TB drain timing: wait_ft_clk(20) after FIFO empty before counting
    - Add exact 2048 Doppler count assertion + handshake race checks
    - Clean up verbose debug instrumentation from off-by-one investigation
2026-04-07 docs(readme): add Alpha disclaimer to Key Features
    Core hardware works, but GPS/map integration, attitude correction,
    and beam steering UI are not yet complete — callers deserve to know
    before they build on those features.
    Closes gap 10.5 from reality-check review.
2026-04-20 test(fpga): F-2.2 adversarial mid-frame reset sweep + F-0.1 TB plumbing
    G9B adds a 4-iteration reset sweep on top of the existing e2e harness:
    - Reset is injected at four offsets (3/7/12/18 us) into a steady-state
    auto-scan burst, with mixed short/long hold durations (20-120 clk_100m)
    to exercise asynchronous assert paths through the FSM + CDCs.
    - Each iteration asserts: system_status drops to 0 during reset,
    new_chirp_frame resumes post-release, and obs_range_valid_count
2026-04-20 fix(fpga): F-0.9 option B — FT2232H output_delay 11.667→3.5 ns (TN_167)
    Previous output_delay of 11.667 ns was a synthetic back-calculation
    (period − 5 ns), not a datasheet number. It over-constrained FPGA
    launch by ~8 ns vs the actual FT2232H 245-Sync FIFO setup requirement.
    Per FTDI TN_167:
    - t_su (data to CLKOUT rising): 3.5 ns (was 11.667 — too tight)
    - t_h (data hold after CLKOUT): 1.0 ns (was 0.0 — no hold check)
2026-04-20 merge(wave3/tier2): port testbenches and cosim goldens for fft-2048
    Regression goes from 21/32 -> 27/32 passing.
    TB files updated from feat/fft-2048-upgrade (FFT_SIZE=2048 / 512 range
    bins / Manhattan magnitude / 2-segment matched filter):
    - tb/tb_mf_cosim.v (range_profile_{i,q} port names)
    - tb/tb_matched_filter_processing_chain.v (long_chirp port names)
    - tb/tb_range_bin_decimator.v (new 2048->512 DUT)
2026-04-23 fix: MCU-N4 delay_us bound; GUI-S4 STREAM_CONTROL comment
    MCU-N4: delay_us(us) reset TIM1 then waited for the counter to reach `us`,
    but TIM1 ARR is 0xffff-1 (~65 ms at the 1 MHz tick). Any caller passing
    us > 65534 spun forever after the first wrap — a real hazard with the PA
    energized. Chunk requests larger than ARR into ARR-sized waits, then the
    remainder in the existing single wait. Current callers (T1, PRI1-T1,
    Guard, 500us spots) are all well under the bound; this is defensive.
2026-04-27 fix(gui): GUI-S2 — DataRecorder snapshots arrays before HDF5 write
    The same RadarFrame is enqueued for the display consumer and handed to
    DataRecorder.record_frame on the producer thread. h5py releases the GIL
    during gzip compression, so any in-place mutation by the consumer (or a
    future scaling/normalisation step) would tear the on-disk frame.
    record_frame now copies all five numpy arrays into local snapshots
    before passing them to h5py.create_dataset. Disk integrity no longer
2026-04-29 xdc(200t): pin AD9484 OR LVDS pair to U20/V20 (L11_T1_SRCC_14)
    Closes AUDIT-C15. The 200T XDC `adc_or_p/n` PACKAGE_PIN was a TODO
    placeholder that blocked all 200T synth/impl with unplaced-IO errors.
    Pins U20/V20 are L11P/L11N_T1_SRCC_14 — same T1 clock tile as adc_dco_p
    on L12_MRCC (W19/W20), so OR captures with the same IBUFDS->BUFIO->IDDR
    source-synchronous topology as adc_d_p[*]. Free-pair confirmed by Vivado
    get_package_pins query against xc7a200tfbg484-2.
2026-04-29 AUDIT-C16: parameterize NUM_CELLS + sample_counter width for 200T
    Pre-fix usb_data_interface.v hardcoded `localparam [14:0] NUM_CELLS =
    15'd16384` for the 50T 512-range x 32-doppler layout. On 200T builds
    with SUPPORT_LONG_RANGE defined, RP_MAX_OUTPUT_BINS=4096 makes a real
    frame 131072 cells, so the fixed value caused two distinct defects:
    (a) value: counter wrapped 8x per real frame; bit-7 frame-start
    marker fired 8x at incorrect host-frame offsets, silently
2026-04-30 chirp-v2 PR-C: chirp_reference_rom replaces chirp_memory_loader_param
    Drop the chirp-v1 1-bit use_long_chirp memory loader and its 6 .mem files;
    introduce chirp_reference_rom — wave_sel-native, single 8192x16 BRAM array
    per Q15 lane, 4-region init (SHORT, MEDIUM, LONG seg0/seg1) loaded from the
    PR-B mem files. Same 1-clk read latency as the legacy module so the RX-B
    autocorrelation alignment fix carries through unchanged.
    Receiver-side wave_sel shim added in radar_receiver_final.v:
2026-05-01 test(diagnostic): PR-J.1 — tb_mf_long_chirp localises LONG-chirp hang
    Standalone diagnostic TB that drives a single chirp (SHORT/MEDIUM/LONG
    selectable via +WAVE=N plusarg) through the production matched_filter
    stack — chirp_reference_rom -> matched_filter_multi_segment ->
    matched_filter_processing_chain (xfft_2048 + frequency_matched_filter)
    — and logs every state transition of:
    ms_state, ch_state, mem_request/mem_ready, segment_request,
2026-05-01 docs(cfar): PR-M.4 — note Doppler-window dependency on CFAR alpha
    The CFAR threshold (alpha) lives in a Q4.4 host register and is loaded
    from RP_DEF_CFAR_ALPHA / _SOFT at boot (3.0 / 1.5 in Q4.4). With PR-M.2
    swapping the Doppler window from a non-canonical "Hamming-ish" LUT
    (PSL=-33 dB) to Dolph-Chebyshev 60 dB (PSL=-60 dB), training-cell
    contamination from off-Doppler sidelobes drops by 27 dB and the
    effective Pfa at the shipped alpha drops accordingly.
2026-05-02 sim(antenna): add OpenEMS aperture-coupled patch model for Stack_Hybrid v2
    Re-simulation infrastructure for the new 4-layer aperture-coupled antenna
    stackup (Stack_Hybrid.png, committed 1de2296). Renders the full multilayer
    geometry (L1 patch / L2 slot ground / L3 microstrip feed / L4 backplane)
    on the actual substrate stack (RO4350B 0.508 mm + RO4450F 1.2 mm + RO4350B
    0.11 mm) and runs FDTD via openEMS to characterize S11 vs frequency.
    Geometry interpolated from existing 2-layer Gerber:
2026-05-05 test(fpga): PR-X.1 F-7.4 — gate tb_ad9484_xsim on MMCM lock (closes PR-N #86)
    Stage-7 ADC chain audit. The MMCM SIMULATION model in adc_clk_mmcm.v
    takes 4096 DCO cycles (~10 µs at 400 MHz) to assert mmcm_locked. The
    existing TB waited only ~5 cycles after each reset deassert, so the
    gated reset_n_400m never released and adc_data_valid_400m stayed low
    for every test group past the initial reset checks.
    Expose mmcm_locked as a new module output on ad9484_interface_400m
2026-05-06 fix(fpga): PR-AA — doppler_mag 1-cell shift in usb emit FSM
    The WR_DOPPLER_DATA emit advanced mag_rd_addr at end of phase 1 (LSB byte)
    but BRAM has 1-cycle read latency, so phase 0 of the next pair re-read
    the prior cell. Result: wire pair K = (HIGH(bram[K-1]), LOW(bram[K])) —
    adjacent cells silently swapped their high bytes whenever the high byte
    differed. Footprint was 30 of 24576 cells (peak rows + high-byte
    transitions in the noise floor); max diff 6656 LSB on the target row.

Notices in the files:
README.md:
Hardware: CERN-OHL-P
